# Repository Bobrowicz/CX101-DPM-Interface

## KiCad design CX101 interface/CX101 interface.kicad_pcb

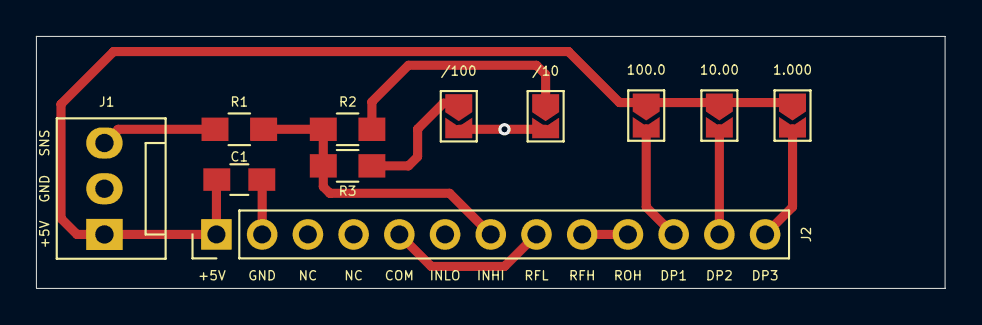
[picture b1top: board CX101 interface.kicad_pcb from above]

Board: 2 copper layers, 50.5 x 14.0 mm, 11 parts (0 on the bottom side), 11 nets.

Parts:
1.000, 10.00, 100.0: SolderJumper_2_Open; SolderJumper-2_P1.3mm_Open_TrianglePad1.0x1.5mm
/10, /100: SolderJumper_2_Open; SolderJumper-2_P1.3mm_Open_TrianglePad1.0x1.5mm
C1: 1u; C_0805_HandSoldering
J1: Conn_01x03_Male; Fan_Pin_Header_Straight_1x03
J2: Conn_01x13_Female; Pin_Header_Straight_1x13_Pitch2.54mm
R1: 1M; R_0805_HandSoldering
R2: 110k; R_0805_HandSoldering
R3: 10k; R_0805_HandSoldering

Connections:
+5V: 1.000.1, 10.00.1, 100.0.1, C1.1, J1.1, J2.1
GND: /10.2, /100.2, C1.2, J1.2, J2.2, J2.6
unnamed: J1.3, R1.2
unnamed: J2.5, J2.8
unnamed: J2.7, R1.1, R2.2, R3.2
unnamed: J2.9, J2.10
unnamed: 100.0.2, J2.11
unnamed: 10.00.2, J2.12
unnamed: 1.000.2, J2.13
unnamed: /10.1, R2.1
unnamed: /100.1, R3.1

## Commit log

2021-03-19 Finished PCB
